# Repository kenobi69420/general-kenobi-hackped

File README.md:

This is my hackpad yeah um idk what to say 
its a macropad 
made too be used with asseto corsa thats why its got some odd keybids

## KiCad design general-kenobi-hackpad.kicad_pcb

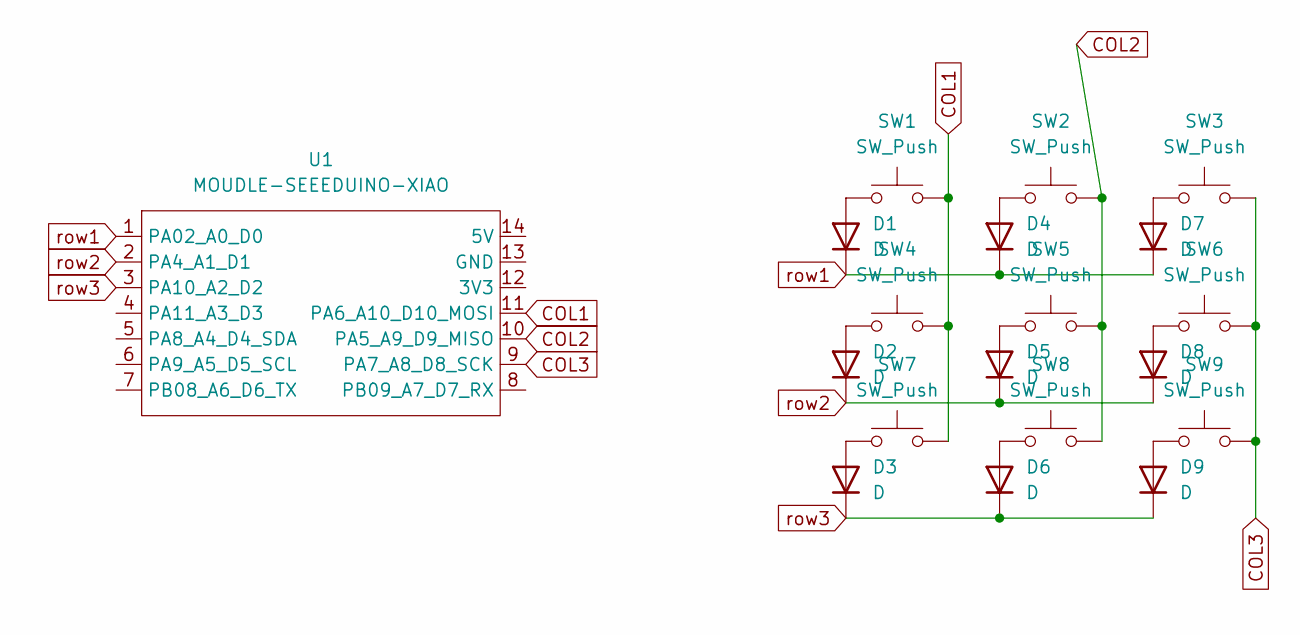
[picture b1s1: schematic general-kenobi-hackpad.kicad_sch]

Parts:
D1, D2, D3, D4, D5, D6, D7, D8, D9: D; D_DO-35_SOD27_P7.62mm_Horizontal
SW1, SW2, SW3, SW4, SW5, SW6, SW7, SW8, SW9: SW_Push; SW_Cherry_MX_1.00u_PCB
U1: MOUDLE-SEEEDUINO-XIAO; XIAO-Generic-Hybrid-14P-2.54-21X17.8MM

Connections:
COL1: SW1.2, SW4.2, SW7.2, U1.11 (PA6_A10_D10_MOSI)
COL2: SW2.2, SW5.2, SW8.2, U1.10 (PA5_A9_D9_MISO)
COL3: SW3.2, SW6.2, SW9.2, U1.9 (PA7_A8_D8_SCK)
unnamed: D1.2 (A), SW1.1
unnamed: D2.2 (A), SW4.1
unnamed: D3.2 (A), SW7.1
unnamed: D4.2 (A), SW2.1
unnamed: D5.2 (A), SW5.1
unnamed: D6.2 (A), SW8.1
unnamed: D7.2 (A), SW3.1
unnamed: D8.2 (A), SW6.1
unnamed: D9.2 (A), SW9.1
row1: D1.1 (K), D4.1 (K), D7.1 (K), U1.1 (PA02_A0_D0)
row2: D2.1 (K), D5.1 (K), D8.1 (K), U1.2 (PA4_A1_D1)
row3: D3.1 (K), D6.1 (K), D9.1 (K), U1.3 (PA10_A2_D2)

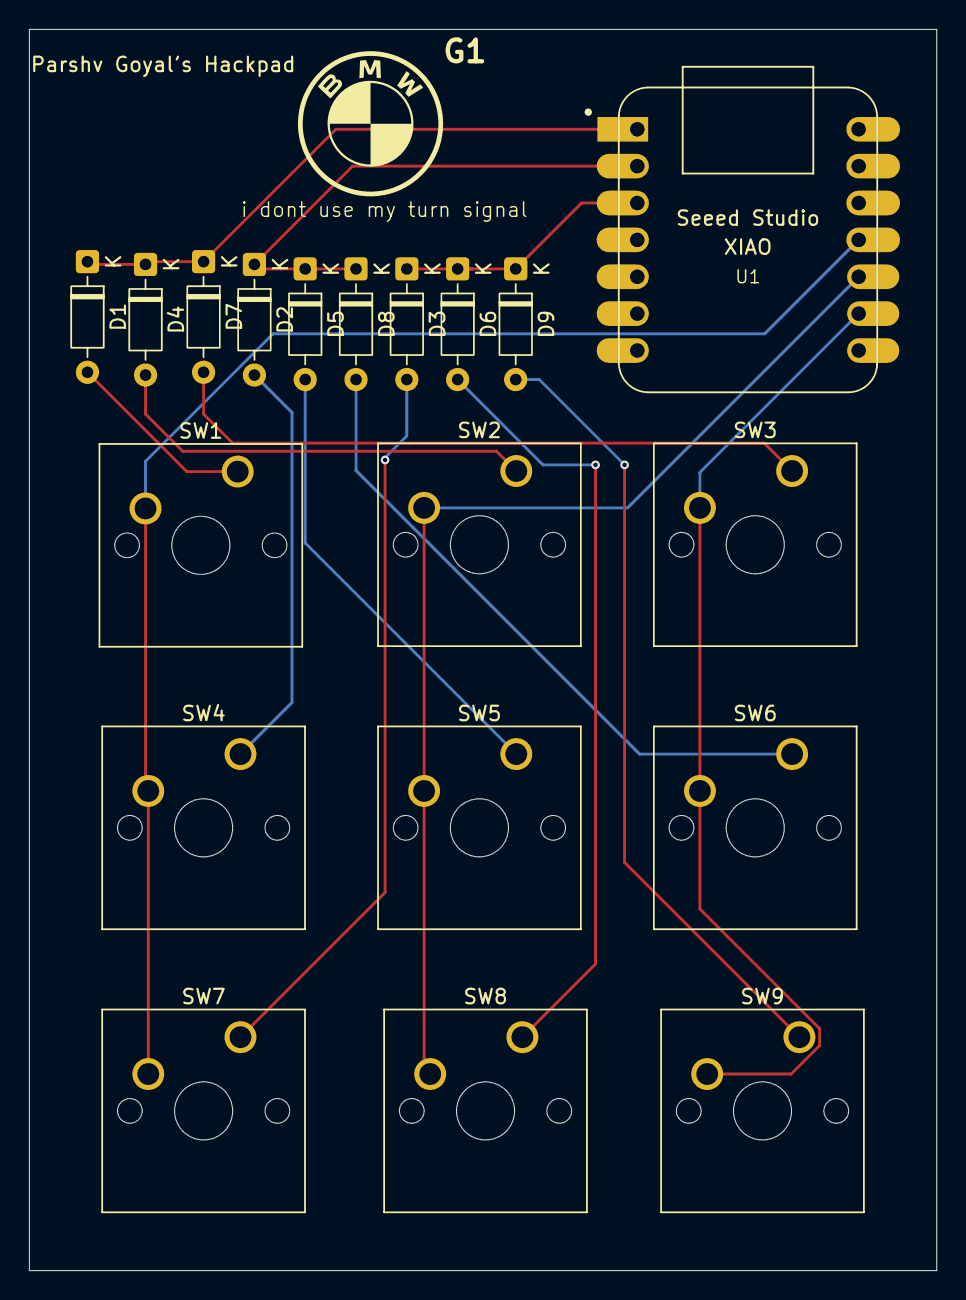
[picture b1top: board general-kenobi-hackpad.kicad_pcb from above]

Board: 2 copper layers, 62.5 x 85.5 mm, 20 parts (0 on the bottom side), 15 nets.

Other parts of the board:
G1: LOGO; bmv
